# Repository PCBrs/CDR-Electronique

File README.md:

# CDR-Electronique
Carte électronique pour la Coupe de France de robotique de l'équipe PCBrs.

La carte principale est basée sur une Teensy 4.1, la communication est faite par Wi-Fi via un ESP32 et la communication interne du robot via un bus CAN. Les cartes sont modulaires et spécifiques, on peut ajouter plusieurs fois le meme types de cartes il faut juste changer l'ID CAN de la carte en soft. Le microcontroleur des cartes périphériques est un STM32F302C8T6. 

Les cartes ont été conçus sur Kicad.

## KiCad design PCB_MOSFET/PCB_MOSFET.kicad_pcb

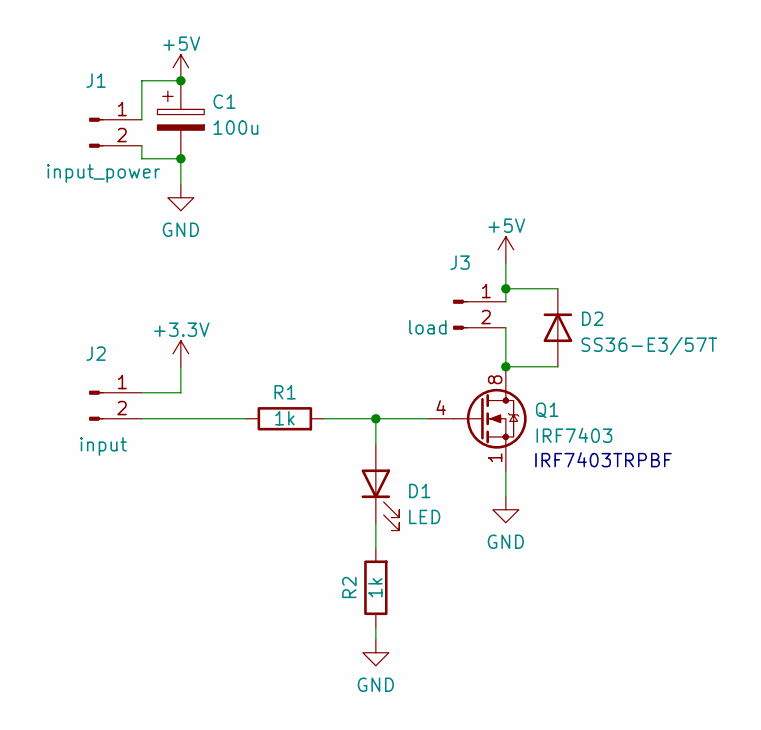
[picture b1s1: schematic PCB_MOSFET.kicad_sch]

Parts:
C1: 100u; CP_Elec_6.3x7.7
D1: LED; LED_0805_2012Metric
D2: SS36-E3/57T; D_SMC
J1: input_power; Wuerth_3.96mm_2pin_645002114822
J2: input; Wuerth_2.54mm_2pins_61900211121
J3: load; Wuerth_3.96mm_2pin_645002114822
Q1: IRF7403; SOIC-8_3.9x4.9mm_P1.27mm
R1, R2: 1k; R_0805_2012Metric

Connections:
+3V3: J2.1
+5V: C1.1, D2.1 (K), J1.1, J3.1
GND: C1.2, J1.2, Q1.1 (S), Q1.2 (S), Q1.3 (S), R2.1
unnamed: D1.1 (K), R2.2
unnamed: D1.2 (A), Q1.4 (G), R1.2
unnamed: D2.2 (A), J3.2, Q1.5 (D), Q1.6 (D), Q1.7 (D), Q1.8 (D)
unnamed: J2.2, R1.1

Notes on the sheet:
IRF7403TRPBF

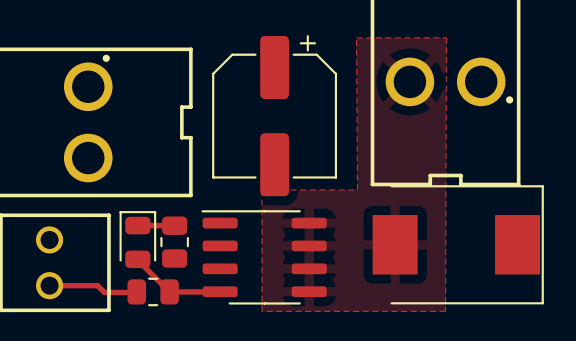
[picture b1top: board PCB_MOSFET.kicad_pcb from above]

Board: 2 copper layers, 9 parts (0 on the bottom side), 6 nets.

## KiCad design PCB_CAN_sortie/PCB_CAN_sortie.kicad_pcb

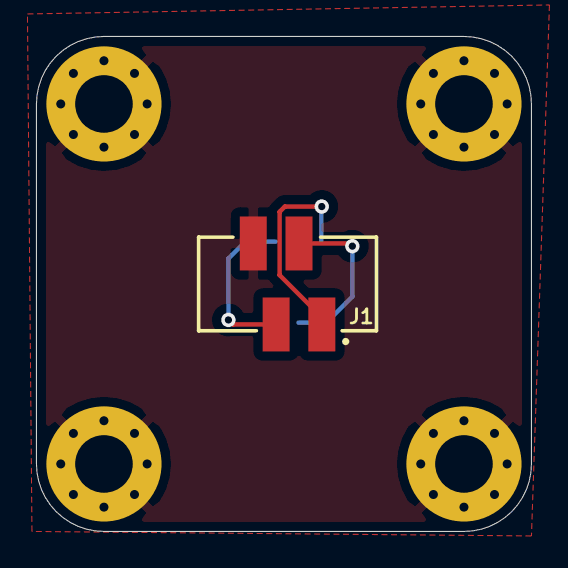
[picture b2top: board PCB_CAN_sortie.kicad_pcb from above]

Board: 2 copper layers, 27.5 x 27.5 mm, 6 parts (1 on the bottom side), 4 nets.

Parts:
H1, H2, H3, H4: .; MountingHole_3.2mm_M3_Pad_Via
J1, J2: CAN; 690367290476

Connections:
+5V: J1.1, J2.1
/CANH: J1.2, J2.2
/CANL: J1.3, J2.3
GND: H1.1, H2.1, H3.1, H4.1, J1.4, J2.4

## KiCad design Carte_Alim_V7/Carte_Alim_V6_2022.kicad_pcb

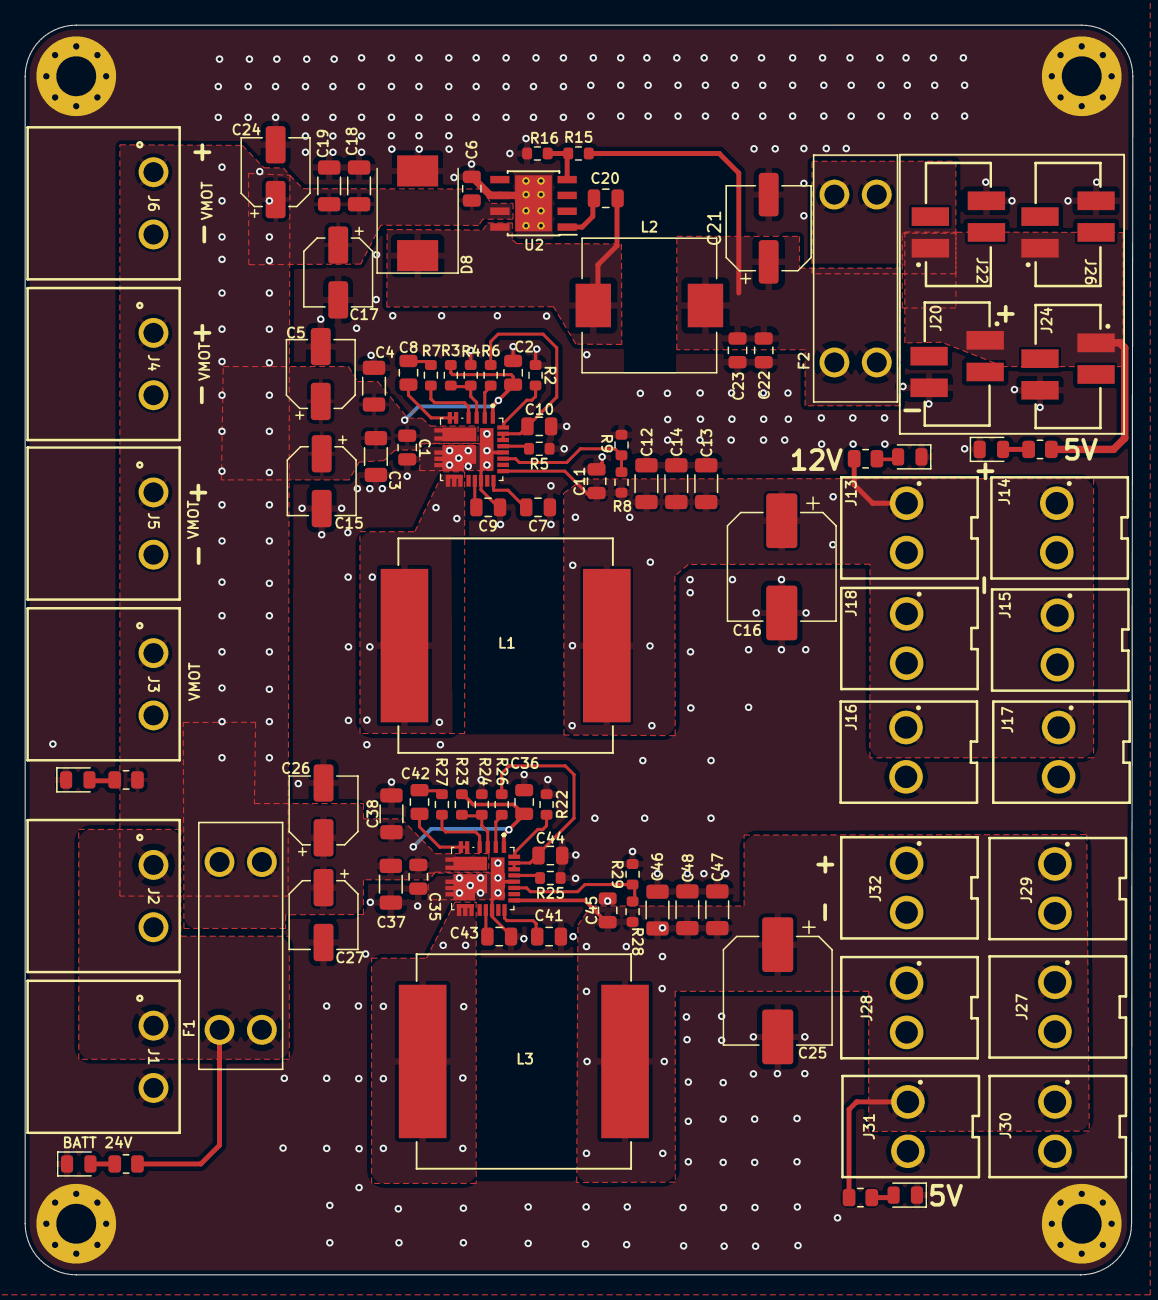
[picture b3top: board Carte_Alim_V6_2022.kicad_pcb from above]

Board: 4 copper layers, 88.9 x 100.3 mm, 102 parts (0 on the bottom side), 39 nets.

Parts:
C1, C2, C6, C8, C11, C22, C35, C36, C42, C45: 100n; C_0805_2012Metric
C3, C4, C12, C13, C14, C18, C19, C37, C38, C46, C47, C48: 22u; C_1206_3216Metric
C5, C15, C17, C24, C26, C27: 10u/50V; CP_Elec_5x5.4
C7, C41: 33n; C_0805_2012Metric
C9, C10, C43, C44: 1u; C_0805_2012Metric
C16, C25: 330u/25V; CP_Elec_8x10.5
C20, C23: 10n; C_0805_2012Metric
C21: 330u; CP_Elec_6.3x7.7
D1, D2, D3, D5, D6: LED; LED_0805_2012Metric
D8: SSC54-E3/9AT; D_SMC
F1, F2: 3557-2; FUSE_3557-2
H1, H2, H3, H4: M3; MountingHole_3.2mm_M3_Pad_Via
J1, J2: BAT_IN; Wuerth_batcon_691313710002
J3, J4, J5, J6: MOT_OUT; Wuerth_batcon_691313710002
J13, J14, J15, J16, J17, J18: 12VP; Wuerth_3.96mm_2pin_645002114822
J20, J22, J24, J26: 5V_CAN; 690367290476
J27, J28, J29, J30, J31, J32: 5VP; Wuerth_3.96mm_2pin_645002114822
L1, L3: 4.7uH; L_Vishay_IHLP-6767
L2: 10uH; L_Wuerth_HCI-1030
R1, R11: 10K; R_0805_2012Metric
R2, R22: 2k; R_0603_1608Metric
R3, R23: 562k; R_0603_1608Metric
R4, R24: 226k; R_0603_1608Metric
R5, R25: 88.7k; R_0603_1608Metric
R6, R26: 100k; R_0603_1608Metric
R7, R27: 3.3; R_0603_1608Metric
R8, R28: 52.3k; R_0603_1608Metric
R9, R15, R29: 10k; R_0603_1608Metric
R10, R30: 10k; R_0805_2012Metric
R13: 560; R_0805_2012Metric
R16: 3k16; R_0603_1608Metric
U1, U3: SIC466ED-T1-GE3; SIC463EDT1GE3
U2: TPS5450ddar; TI_SO-PowerPAD-8_ThermalVias

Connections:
+5P: C25.1, C45.1, C46.1, C47.1, C48.1, J27.1, J28.1, J29.1, J30.1, J31.1, J32.1, L3.2, R28.2, R30.1, U3.20 (VSNS)
+5V: F2.3, J20.1, J22.1, J24.1, J26.1, R13.1
+12P: C11.1, C12.1, C13.1, C14.1, C16.1, J13.1, J14.1, J15.1, J16.1, J17.1, J18.1, L1.2, R8.2, R10.1, U1.20 (VSNS)
+24V: C1.1, C2.1, C3.1, C4.1, C5.1, C6.1, C15.1, C17.1, C18.1, C19.1, C24.1, C26.1, C27.1, C35.1, C36.1, C37.1, C38.1, F1.3, J3.1, J4.1, J5.1, J6.1, R3.1, R11.1, R23.1, U1.1 (VCIN), U1.7 (VIN), U1.8 (VIN), U1.29 (VIN), U2.7 (VIN), U3.1 (VCIN), U3.7 (VIN), U3.8 (VIN), U3.29 (VIN)
+BATT: F1.1, J1.1, J2.1, R1.1
/REGULO2/VDD: C44.2, R26.1, U3.25 (ILIMIT), U3.26 (VDD)
/REGULO5v/VSENS: R15.2, R16.1, U2.4 (VSENSE)
/REGULO/VDD: C10.2, R6.1, U1.25 (ILIMIT), U1.26 (VDD)
GND: C1.2, C2.2, C3.2, C4.2, C5.2, C6.2, C7.2, C9.1, C10.1, C11.2, C12.2, C13.2, C14.2, C15.2, C16.2, C17.2, C18.2, C19.2, C21.2, C22.2, C23.2, C24.2, C25.2, C26.2, C27.2, C35.2, C36.2, C37.2, C38.2, C41.2, C43.1, C44.1, C45.2, C46.2, C47.2, C48.2, D1.1 (K), D2.1 (K), D3.1 (K), D5.1 (K), D6.1 (K), D8.2 (A), H1.1, H2.1, H3.1, H4.1, J1.2, J2.2, J3.2, J4.2, J5.2, J6.2, J13.2, J14.2, J15.2, J16.2, J17.2, J18.2, J20.4, J22.4, J24.4, J26.4, J27.2, J28.2, J29.2, J30.2, J31.2, J32.2, R2.2, R4.2, R5.2, R9.1, R16.2, R22.2, R24.2, R25.2, R29.1, U1.9 (PGND), U1.10 (PGND), U1.11 (PGND), U1.17 (PGND), U1.23 (AGND), U1.28 (AGND), U1.30 (PGND), U1.A30 (PGND), U2.6 (GND), U2.9 (GNDPAD), U3.9 (PGND), U3.10 (PGND), U3.11 (PGND), U3.17 (PGND), U3.23 (AGND), U3.28 (AGND), U3.30 (PGND), U3.A30 (PGND)
unnamed: C7.1, U1.19 (SS)
unnamed: C8.1, R7.2
unnamed: C8.2, U1.5 (PHASE), U1.6 (PHASE)
unnamed: C9.2, U1.16 (VDRV)
unnamed: C20.1, D8.1 (K), L2.1, U2.8 (PH)
unnamed: C20.2, U2.1 (BOOT)
unnamed: C21.1, C22.1, C23.1, F2.1, L2.2, R15.1
unnamed: C41.1, U3.19 (SS)
unnamed: C42.1, R27.2
unnamed: C42.2, U3.5 (PHASE), U3.6 (PHASE)
unnamed: C43.2, U3.16 (VDRV)
unnamed: D1.2 (A), R1.2
unnamed: D2.2 (A), R10.2
unnamed: D3.2 (A), R11.2
unnamed: D5.2 (A), R13.2
unnamed: D6.2 (A), R30.2
unnamed: L1.1, U1.12 (SW), U1.13 (SW), U1.14 (SW), U1.A12
unnamed: L3.1, U3.12 (SW), U3.13 (SW), U3.14 (SW), U3.A12
unnamed: R2.1, U1.27 (MODE)
unnamed: R3.2, R4.1, U1.3 (EN)
unnamed: R5.1, U1.24 (FSW)
unnamed: R6.2, U1.2 (PGOOD)
unnamed: R7.1, U1.4 (BOOT)
unnamed: R8.1, R9.2, U1.22 (VFB)
unnamed: R22.1, U3.27 (MODE)
unnamed: R23.2, R24.1, U3.3 (EN)
unnamed: R25.1, U3.24 (FSW)
unnamed: R26.2, U3.2 (PGOOD)
unnamed: R27.1, U3.4 (BOOT)
unnamed: R28.1, R29.2, U3.22 (VFB)

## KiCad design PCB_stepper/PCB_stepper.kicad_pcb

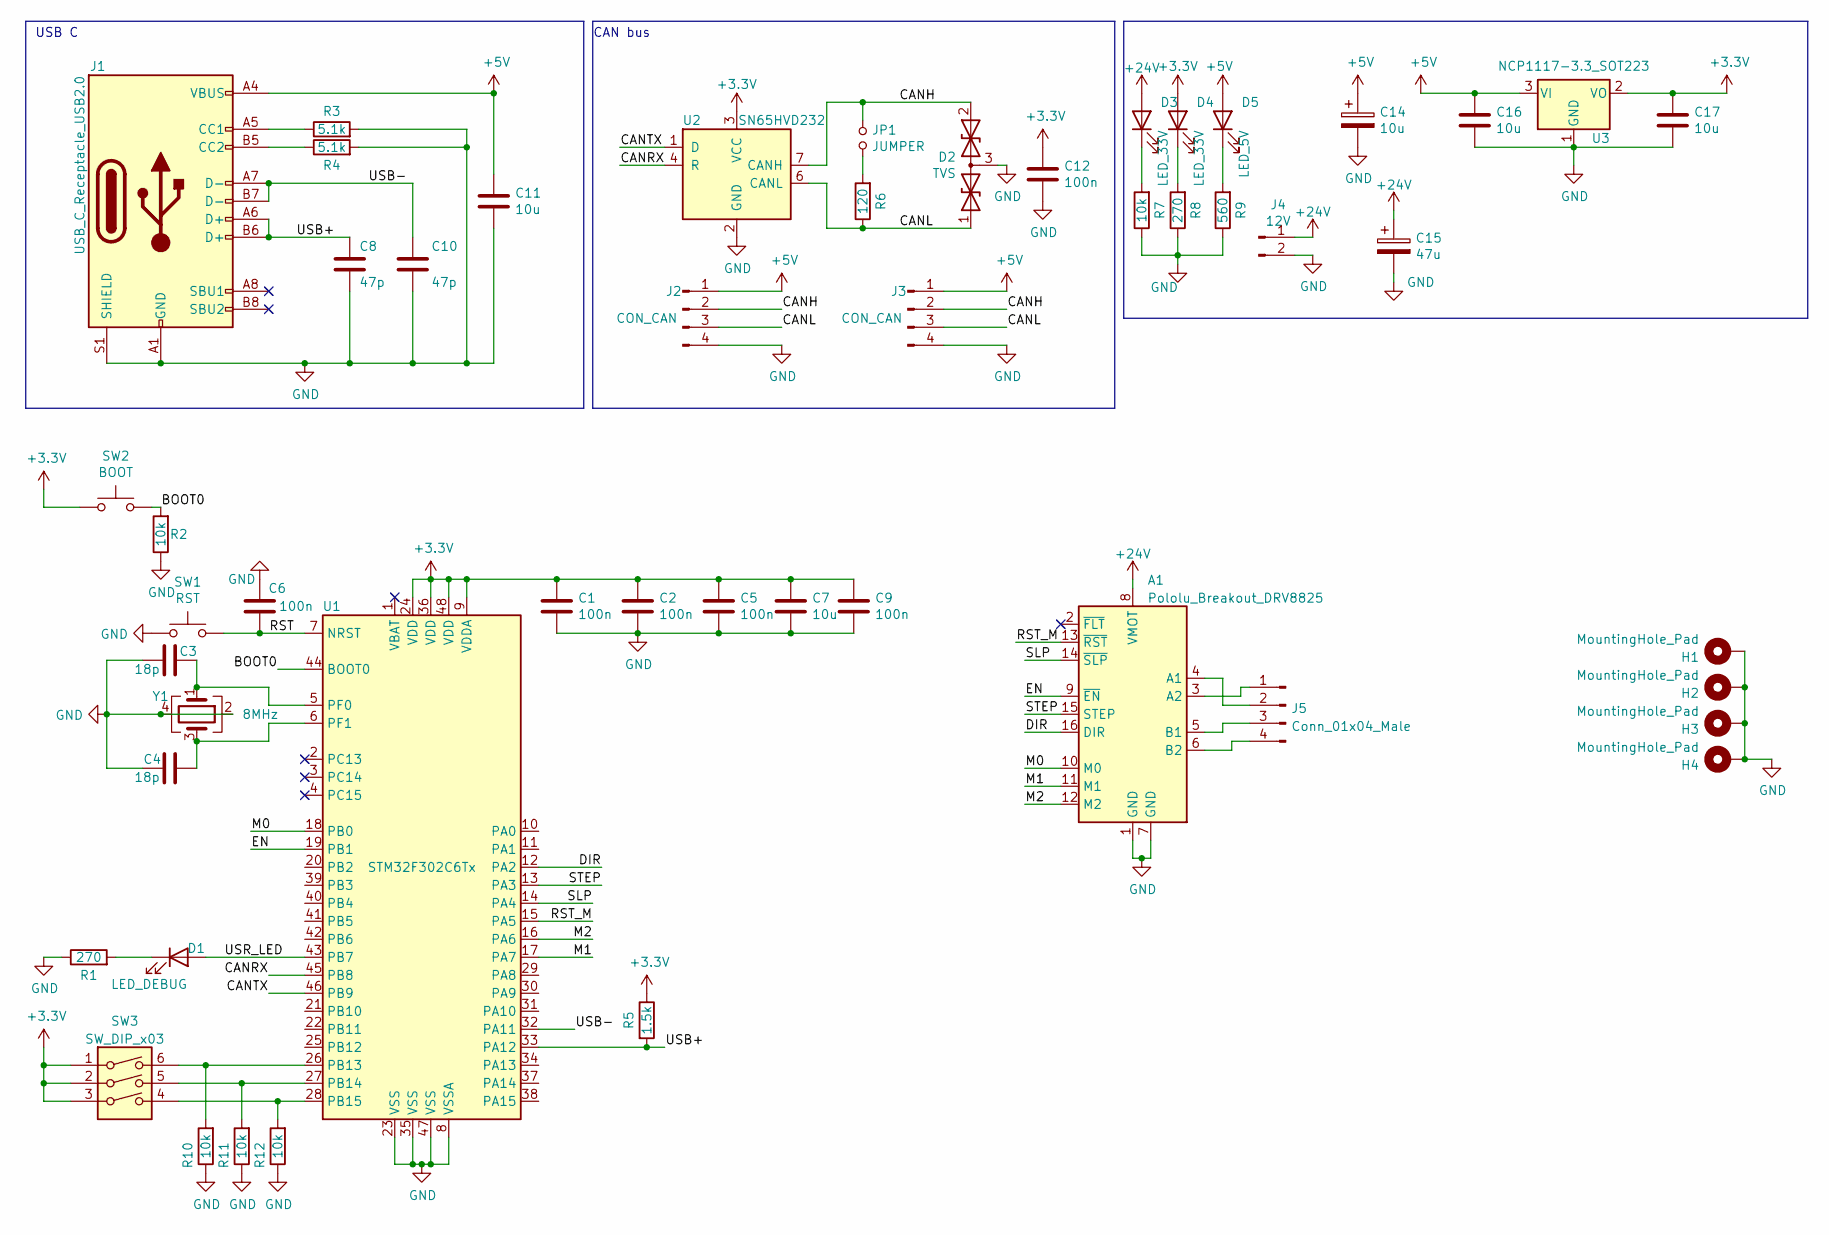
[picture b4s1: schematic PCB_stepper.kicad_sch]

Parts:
A1: Pololu_Breakout_DRV8825; Pololu_Breakout-16_15.2x20.3mm
C1, C2, C5, C6, C9, C12: 100n; C_0805_2012Metric
C3, C4: 18p; C_0805_2012Metric
C7, C11, C16, C17: 10u; C_0805_2012Metric
C8, C10: 47p; C_0805_2012Metric
C14: 10u; CP_Elec_5x5.4
C15: 47u; CP_Elec_6.3x5.4
D1: LED_DEBUG; LED_0805_2012Metric
D2: TVS; SOT-23
D3, D4: LED_33V; LED_0805_2012Metric
D5: LED_5V; LED_0805_2012Metric
H1, H2, H3, H4: MountingHole_Pad; MountingHole_3.2mm_M3_Pad_Via
J1: USB_C_Receptacle_USB2.0; USB_C_Receptacle_GCT_USB4085
J2, J3: CON_CAN; 690367290476
J4: 12V; Wuerth_batcon_691313710002
J5: Conn_01x04_Male; Wuerth_2.54mm_4pins_61900411121
JP1: JUMPER; PinHeader_1x02_P2.54mm_Vertical
R1, R8: 270; R_0805_2012Metric
R2, R7, R10, R11, R12: 10k; R_0805_2012Metric
R3, R4: 5.1k; R_0805_2012Metric
R5: 1.5k; R_0805_2012Metric
R6: 120; R_0805_2012Metric
R9: 560; R_0805_2012Metric
SW1: RST; SW_SPST_CK_RS282G05A3
SW2: BOOT; SW_SPST_CK_RS282G05A3
SW3: SW_DIP_x03; SW_DIP_SPSTx03_Slide_KingTek_DSHP03TJ_W5.25mm_P1.27mm_JPin
U1: STM32F302C6Tx; LQFP-48_7x7mm_P0.5mm
U2: SN65HVD232; SOIC-8_3.9x4.9mm_P1.27mm
U3: NCP1117-3.3_SOT223; SOT-223-3_TabPin2
Y1: 8MHz; Crystal_SMD_5032-4Pin_5.0x3.2mm

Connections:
+3V3: C1.1, C2.1, C5.1, C7.1, C9.1, C12.1, C17.1, D4.2 (A), R5.1, SW2.1, SW3.1, SW3.2, SW3.3, U1.9 (VDDA), U1.24 (VDD), U1.36 (VDD), U1.48 (VDD), U2.3 (VCC), U3.2 (VO)
+5V: C11.1, C14.1, C16.1, D5.2 (A), J1.A4 (VBUS), J1.A9 (VBUS), J1.B4 (VBUS), J1.B9 (VBUS), J2.1, J3.1, U3.3 (VI)
+24V: A1.8 (VMOT), C15.1, D3.2 (A), J4.1
/BOOT0: R2.2, SW2.2, U1.44 (BOOT0)
/CANH: D2.2 (A2), J2.2, J3.2, JP1.1, U2.7 (CANH); also elsewhere on the board
/CANL: D2.1 (A1), J2.3, J3.3, R6.1, U2.6 (CANL)
/CANRX: U1.45 (PB8), U2.4 (R)
/CANTX: U1.46 (PB9), U2.1 (D)
/DIR: A1.16 (DIR), U1.12 (PA2)
/EN: A1.9 (~EN), U1.19 (PB1)
/M0: A1.10 (M0), U1.18 (PB0)
/M1: A1.11 (M1), U1.17 (PA7)
/M2: A1.12 (M2), U1.16 (PA6)
/RST: C6.1, SW1.2, U1.7 (NRST)
/RST_M: A1.13 (~RST), U1.15 (PA5)
/SLP: A1.14 (~SLP), U1.14 (PA4)
/STEP: A1.15 (STEP), U1.13 (PA3)
/USB+: C8.1, J1.A6 (D+), J1.B6 (D+), R5.2, U1.33 (PA12)
/USB-: C10.1, J1.A7 (D-), J1.B7 (D-), U1.32 (PA11)
/USR_LED: D1.2 (A), U1.43 (PB7)
GND: A1.1 (GND), A1.7 (GND), C1.2, C2.2, C3.2, C4.2, C5.2, C6.2, C7.2, C8.2, C9.2, C10.2, C11.2, C12.2, C14.2, C15.2, C16.2, C17.2, D2.3 (common), H1.1, H2.1, H3.1, H4.1, J1.A1 (GND), J1.A12 (GND), J1.B1 (GND), J1.B12 (GND), J1.S1 (SHIELD), J2.4, J3.4, J4.2, R1.1, R2.1, R3.2, R4.2, R7.1, R8.1, R9.1, R10.1, R11.1, R12.1, SW1.1, U1.8 (VSSA), U1.23 (VSS), U1.35 (VSS), U1.47 (VSS), U2.2 (GND), U3.1 (GND), Y1.2, Y1.4
unnamed: A1.3 (A2), J5.1
unnamed: A1.4 (A1), J5.2
unnamed: A1.5 (B1), J5.3
unnamed: A1.6 (B2), J5.4
unnamed: C3.1, U1.5 (PF0), Y1.1
unnamed: C4.1, U1.6 (PF1), Y1.3
unnamed: D1.1 (K), R1.2
unnamed: D3.1 (K), R7.2
unnamed: D4.1 (K), R8.2
unnamed: D5.1 (K), R9.2
unnamed: J1.A5 (CC1), R3.1
unnamed: J1.B5 (CC2), R4.1
unnamed 33: JP1.2, R6.2; also elsewhere on the board
unnamed: R10.2, SW3.6, U1.26 (PB13)
unnamed: R11.2, SW3.5, U1.27 (PB14)
unnamed: R12.2, SW3.4, U1.28 (PB15)

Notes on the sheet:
USB C
CAN bus

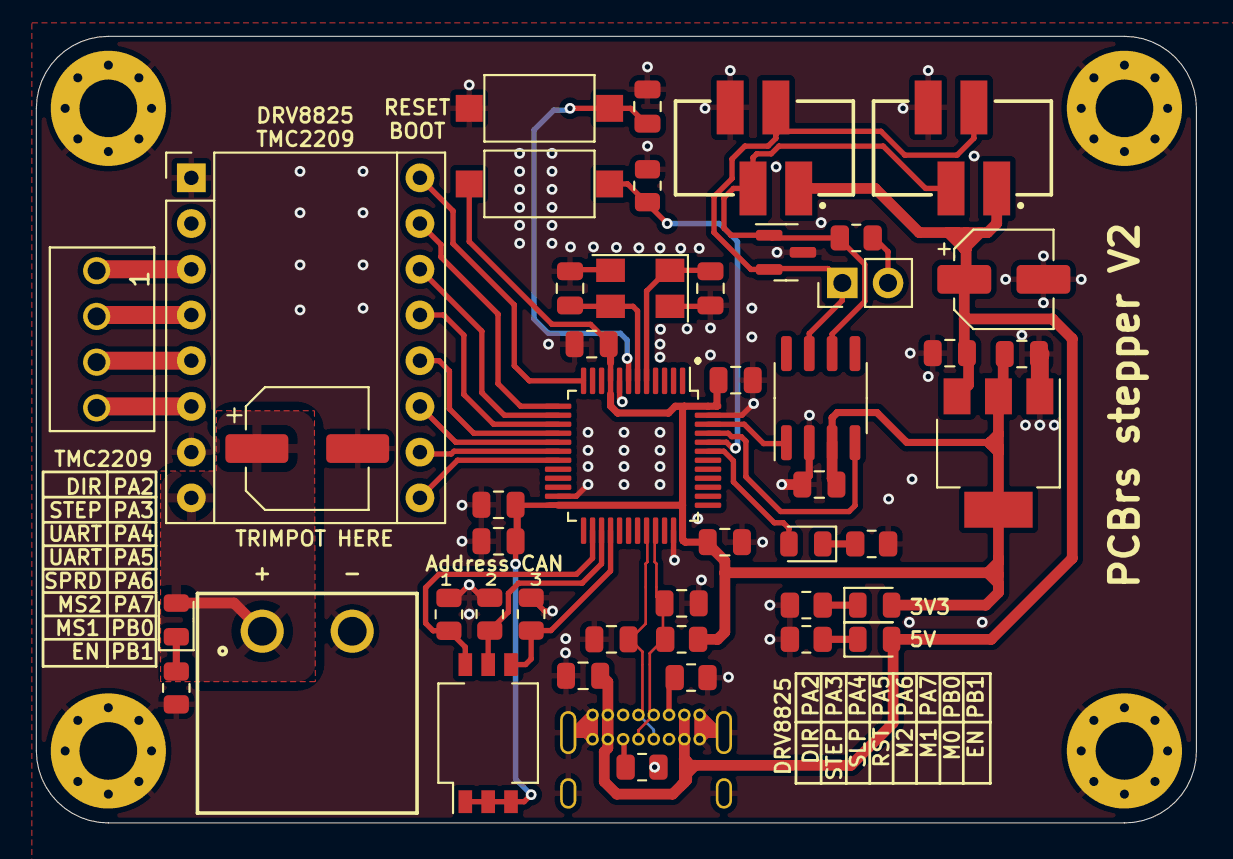
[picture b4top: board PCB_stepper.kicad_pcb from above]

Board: 2 copper layers, 64.4 x 43.7 mm, 51 parts (1 on the bottom side), 37 nets.

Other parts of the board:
120: JUMPER; PinHeader_1x02_P2.54mm_Vertical

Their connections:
/CANH: 120.1; also elsewhere on the board
unnamed 33: 120.2; also elsewhere on the board

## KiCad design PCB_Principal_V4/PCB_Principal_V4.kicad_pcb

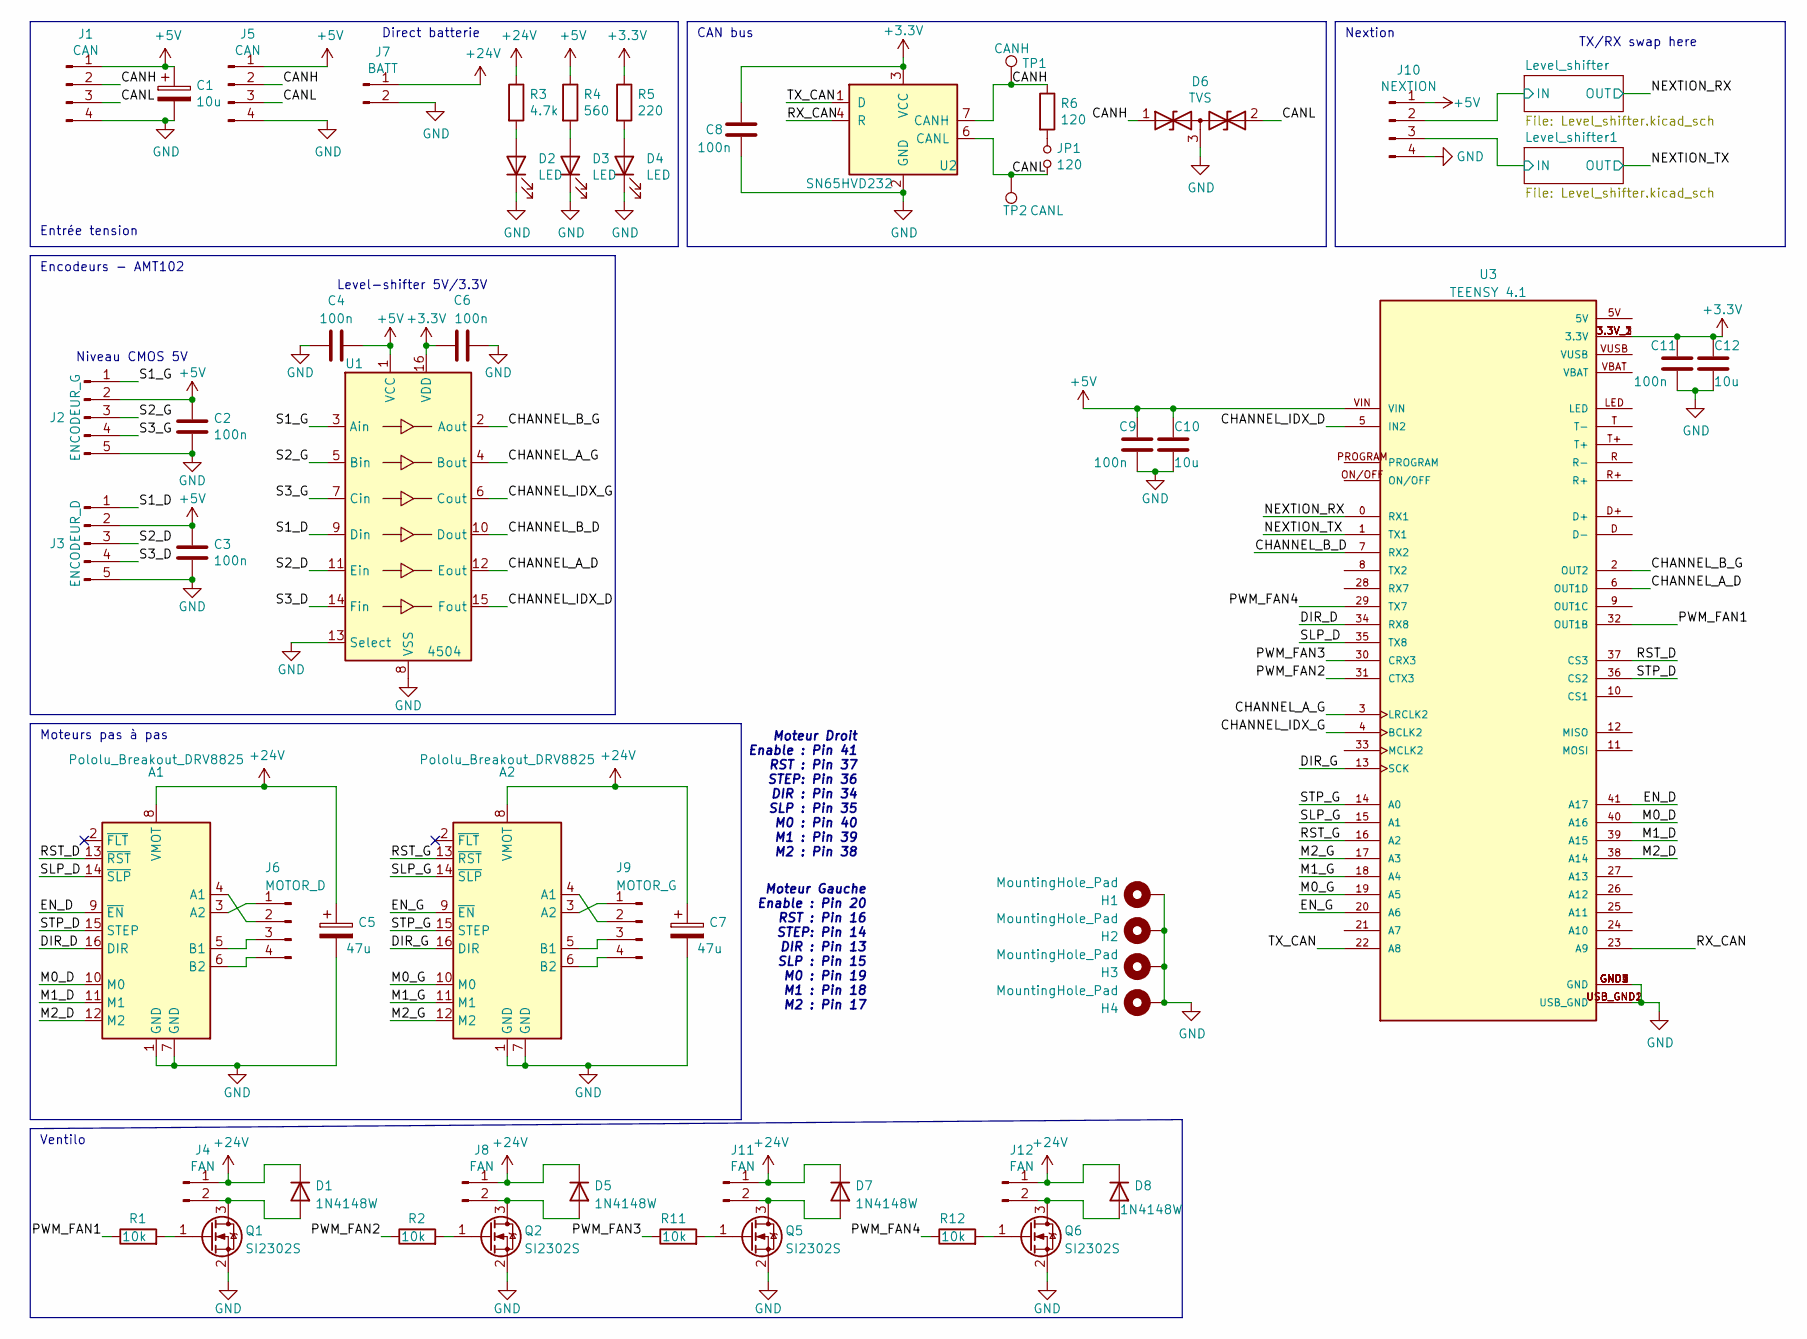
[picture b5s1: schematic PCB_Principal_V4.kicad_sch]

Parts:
A1, A2: Pololu_Breakout_DRV8825; Pololu_Breakout-16_15.2x20.3mm
C1: 10u; CP_Elec_5x5.4
C2, C3, C4, C6, C8, C9, C11: 100n; C_0805_2012Metric_Pad1.18x1.45mm_HandSolder
C5, C7: 47u; CP_Elec_6.3x5.4
C10, C12: 10u; C_0805_2012Metric_Pad1.18x1.45mm_HandSolder
D1, D5, D7, D8: 1N4148W; D_SOD-123
D2, D3, D4: LED; LED_0805_2012Metric_Pad1.15x1.40mm_HandSolder
D6: TVS; SOT-23
H1, H2, H3, H4: MountingHole_Pad; MountingHole_3.2mm_M3_Pad_Via
J1, J5: CAN; 690367290476
J2: ENCODEUR_G; PinHeader_1x05_P2.54mm_Vertical
J3: ENCODEUR_D; PinHeader_1x05_P2.54mm_Vertical
J4, J8, J11, J12: FAN; Wuerth_2.54mm_2pins_61900211121
J6: MOTOR_D; Wuerth_2.54mm_4pins_61900411121
J7: BATT; Wuerth_batcon_691313710002
J9: MOTOR_G; Wuerth_2.54mm_4pins_61900411121
J10: NEXTION; Wuerth_2.54mm_4pins_61900411121
JP1: 120; PinHeader_1x02_P2.54mm_Vertical
Q1, Q2, Q5, Q6: SI2302S; SOT-23
R1, R2, R11, R12: 10k; R_0805_2012Metric_Pad1.20x1.40mm_HandSolder
R3: 4.7k; R_0805_2012Metric_Pad1.20x1.40mm_HandSolder
R4: 560; R_0805_2012Metric_Pad1.20x1.40mm_HandSolder
R5: 220; R_0805_2012Metric_Pad1.20x1.40mm_HandSolder
R6: 120; R_0805_2012Metric_Pad1.20x1.40mm_HandSolder
TP1: CANH; TestPoint_Pad_D1.0mm
TP2: CANL; TestPoint_Pad_D1.0mm
U1: 4504; TSSOP-16_4.4x5mm_P0.65mm
U2: SN65HVD232; SOIC-8_3.9x4.9mm_P1.27mm
U3: TEENSY 4.1; Teensy_4-1; PARTREV 4.1

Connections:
+3V3: C6.2, C8.2, C11.1, C12.1, R5.1, U1.16 (VDD), U2.3 (VCC), U3.3.3V_1 (3.3V), U3.3.3V_2 (3.3V), U3.3.3V_3 (3.3V); also elsewhere on the board
+5V: C1.1, C2.1, C3.1, C4.2, C9.1, C10.1, J1.1, J2.2, J3.2, J5.1, J10.1, R4.1, U1.1 (VCC), U3.VIN; also elsewhere on the board
+24V: A1.8 (VMOT), A2.8 (VMOT), C5.1, C7.1, D1.1 (K), D5.1 (K), D7.1 (K), D8.1 (K), J4.1, J7.1, J8.1, J11.1, J12.1, R3.1
/CANH: D6.1 (A1), J1.2, J5.2, R6.1, TP1.1, U2.7 (CANH)
/CANL: D6.2 (A2), J1.3, J5.3, JP1.2, TP2.1, U2.6 (CANL)
/CHANNEL_A_D: U1.12 (Eout), U3.6 (OUT1D)
/CHANNEL_A_G: U1.4 (Bout), U3.3 (LRCLK2)
/CHANNEL_B_D: U1.10 (Dout), U3.7 (RX2)
/CHANNEL_B_G: U1.2 (Aout), U3.2 (OUT2)
/CHANNEL_IDX_D: U1.15 (Fout), U3.5 (IN2)
/CHANNEL_IDX_G: U1.6 (Cout), U3.4 (BCLK2)
/DIR_D: A1.16 (DIR), U3.34 (RX8)
/DIR_G: A2.16 (DIR), U3.13 (SCK)
/EN_D: A1.9 (~EN), U3.41 (A17)
/EN_G: A2.9 (~EN), U3.20 (A6)
/Level_shifter1/IN: J10.3; also elsewhere on the board
/Level_shifter/IN: J10.2; also elsewhere on the board
/M0_D: A1.10 (M0), U3.40 (A16)
/M0_G: A2.10 (M0), U3.19 (A5)
/M1_D: A1.11 (M1), U3.39 (A15)
/M1_G: A2.11 (M1), U3.18 (A4)
/M2_D: A1.12 (M2), U3.38 (A14)
/M2_G: A2.12 (M2), U3.17 (A3)
/NEXTION_RX: U3.0 (RX1); also elsewhere on the board
/NEXTION_TX: U3.1 (TX1); also elsewhere on the board
/PWM_FAN1: R1.1, U3.32 (OUT1B)
/PWM_FAN2: R2.1, U3.31 (CTX3)
/PWM_FAN3: R11.1, U3.30 (CRX3)
/PWM_FAN4: R12.1, U3.29 (TX7)
/RST_D: A1.13 (~RST), U3.37 (CS3)
/RST_G: A2.13 (~RST), U3.16 (A2)
/RX_CAN: U2.4 (R), U3.23 (A9)
/S1_D: J3.1, U1.9 (Din)
/S1_G: J2.1, U1.3 (Ain)
/S2_D: J3.3, U1.11 (Ein)
/S2_G: J2.3, U1.5 (Bin)
/S3_D: J3.4, U1.14 (Fin)
/S3_G: J2.4, U1.7 (Cin)
/SLP_D: A1.14 (~SLP), U3.35 (TX8)
/SLP_G: A2.14 (~SLP), U3.15 (A1)
/STP_D: A1.15 (STEP), U3.36 (CS2)
/STP_G: A2.15 (STEP), U3.14 (A0)
/TX_CAN: U2.1 (D), U3.22 (A8)
GND: A1.1 (GND), A1.7 (GND), A2.1 (GND), A2.7 (GND), C1.2, C2.2, C3.2, C4.1, C5.2, C6.1, C7.2, C8.1, C9.2, C10.2, C11.2, C12.2, D2.1 (K), D3.1 (K), D4.1 (K), D6.3 (common), H1.1, H2.1, H3.1, H4.1, J1.4, J2.5, J3.5, J5.4, J7.2, J10.4, Q1.2 (E), Q2.2 (E), Q5.2 (E), Q6.2 (E), U1.8 (VSS), U1.13 (Select), U2.2 (GND), U3.GND1 (GND), U3.GND2 (GND), U3.GND3 (GND), U3.GND4 (GND), U3.GND5 (GND), U3.USB_GND1 (USB_GND), U3.USB_GND2 (USB_GND)
unnamed: A1.3 (A2), J6.1
unnamed: A1.4 (A1), J6.2
unnamed: A1.5 (B1), J6.3
unnamed: A1.6 (B2), J6.4
unnamed: A2.3 (A2), J9.1
unnamed: A2.4 (A1), J9.2
unnamed: A2.5 (B1), J9.3
unnamed: A2.6 (B2), J9.4
unnamed: D1.2 (A), J4.2, Q1.3 (C)
unnamed: D2.2 (A), R3.2
unnamed: D3.2 (A), R4.2
unnamed: D4.2 (A), R5.2
unnamed: D5.2 (A), J8.2, Q2.3 (C)
unnamed: D7.2 (A), J11.2, Q5.3 (C)
unnamed: D8.2 (A), J12.2, Q6.3 (C)
unnamed: JP1.1, R6.2
unnamed: Q1.1 (B), R1.2
unnamed: Q2.1 (B), R2.2
unnamed: Q5.1 (B), R11.2
unnamed: Q6.1 (B), R12.2

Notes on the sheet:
Ventilo
Direct batterie
TX/RX swap here
Level-shifter 5V/3.3V
Moteur Gauche Enable : Pin 20 RST : Pin 16 STEP: Pin 14 DIR : Pin 13 SLP : Pin 15 M0 : Pin 19 M1 : Pin 18 M2 : Pin 17
Entrée tension
Nextion
CAN bus
Encodeurs - AMT102
Niveau CMOS 5V
Moteurs pas à pas
Moteur Droit Enable : Pin 41 RST : Pin 37 STEP: Pin 36 DIR : Pin 34 SLP : Pin 35 M0 : Pin 40 M1 : Pin 39 M2 : Pin 38

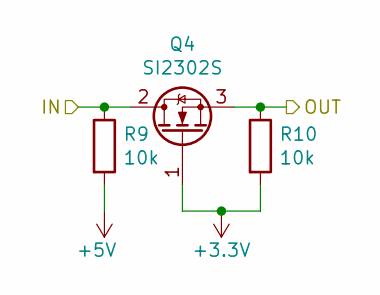
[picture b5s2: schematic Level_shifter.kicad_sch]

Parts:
Q4: SI2302S; SOT-23
R9, R10: 10k; R_0805_2012Metric_Pad1.20x1.40mm_HandSolder

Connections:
+3V3: Q4.1 (G), R10.2; also elsewhere on the board
+5V: R9.2; also elsewhere on the board
/Level_shifter/IN: Q4.2 (D), R9.1; also elsewhere on the board
/NEXTION_RX: Q4.3 (S), R10.1; also elsewhere on the board

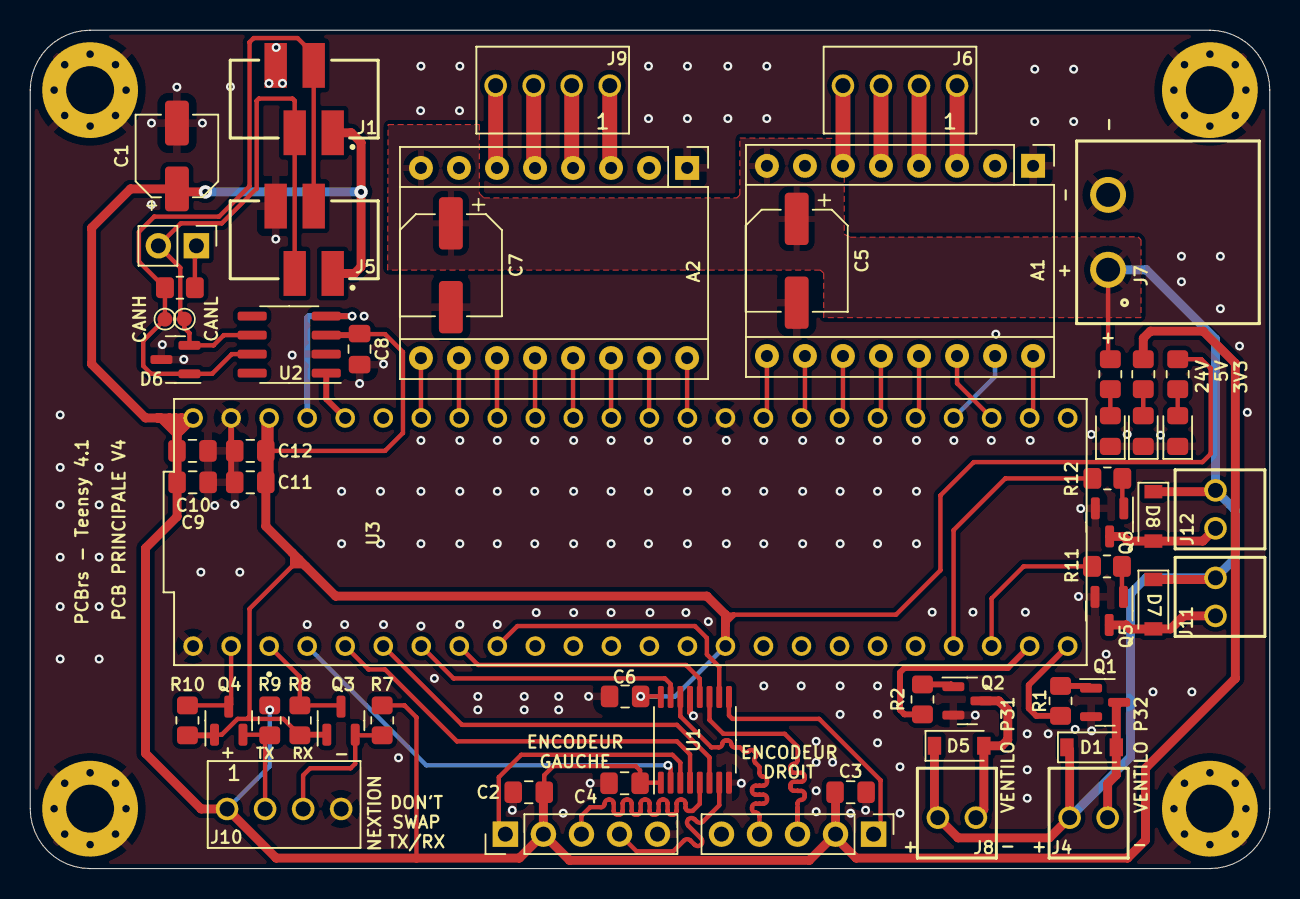
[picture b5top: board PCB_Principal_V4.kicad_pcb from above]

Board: 2 copper layers, 82.8 x 56.0 mm, 62 parts (0 on the bottom side), 64 nets.

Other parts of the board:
Q3: SI2302S; SOT-23
R7, R8: 10k; R_0805_2012Metric_Pad1.20x1.40mm_HandSolder

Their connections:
+3V3: Q3.1 (G), R8.2; also elsewhere on the board
+5V: R7.2; also elsewhere on the board
/Level_shifter1/IN: Q3.2 (D), R7.1; also elsewhere on the board
/NEXTION_TX: Q3.3 (S), R8.1; also elsewhere on the board

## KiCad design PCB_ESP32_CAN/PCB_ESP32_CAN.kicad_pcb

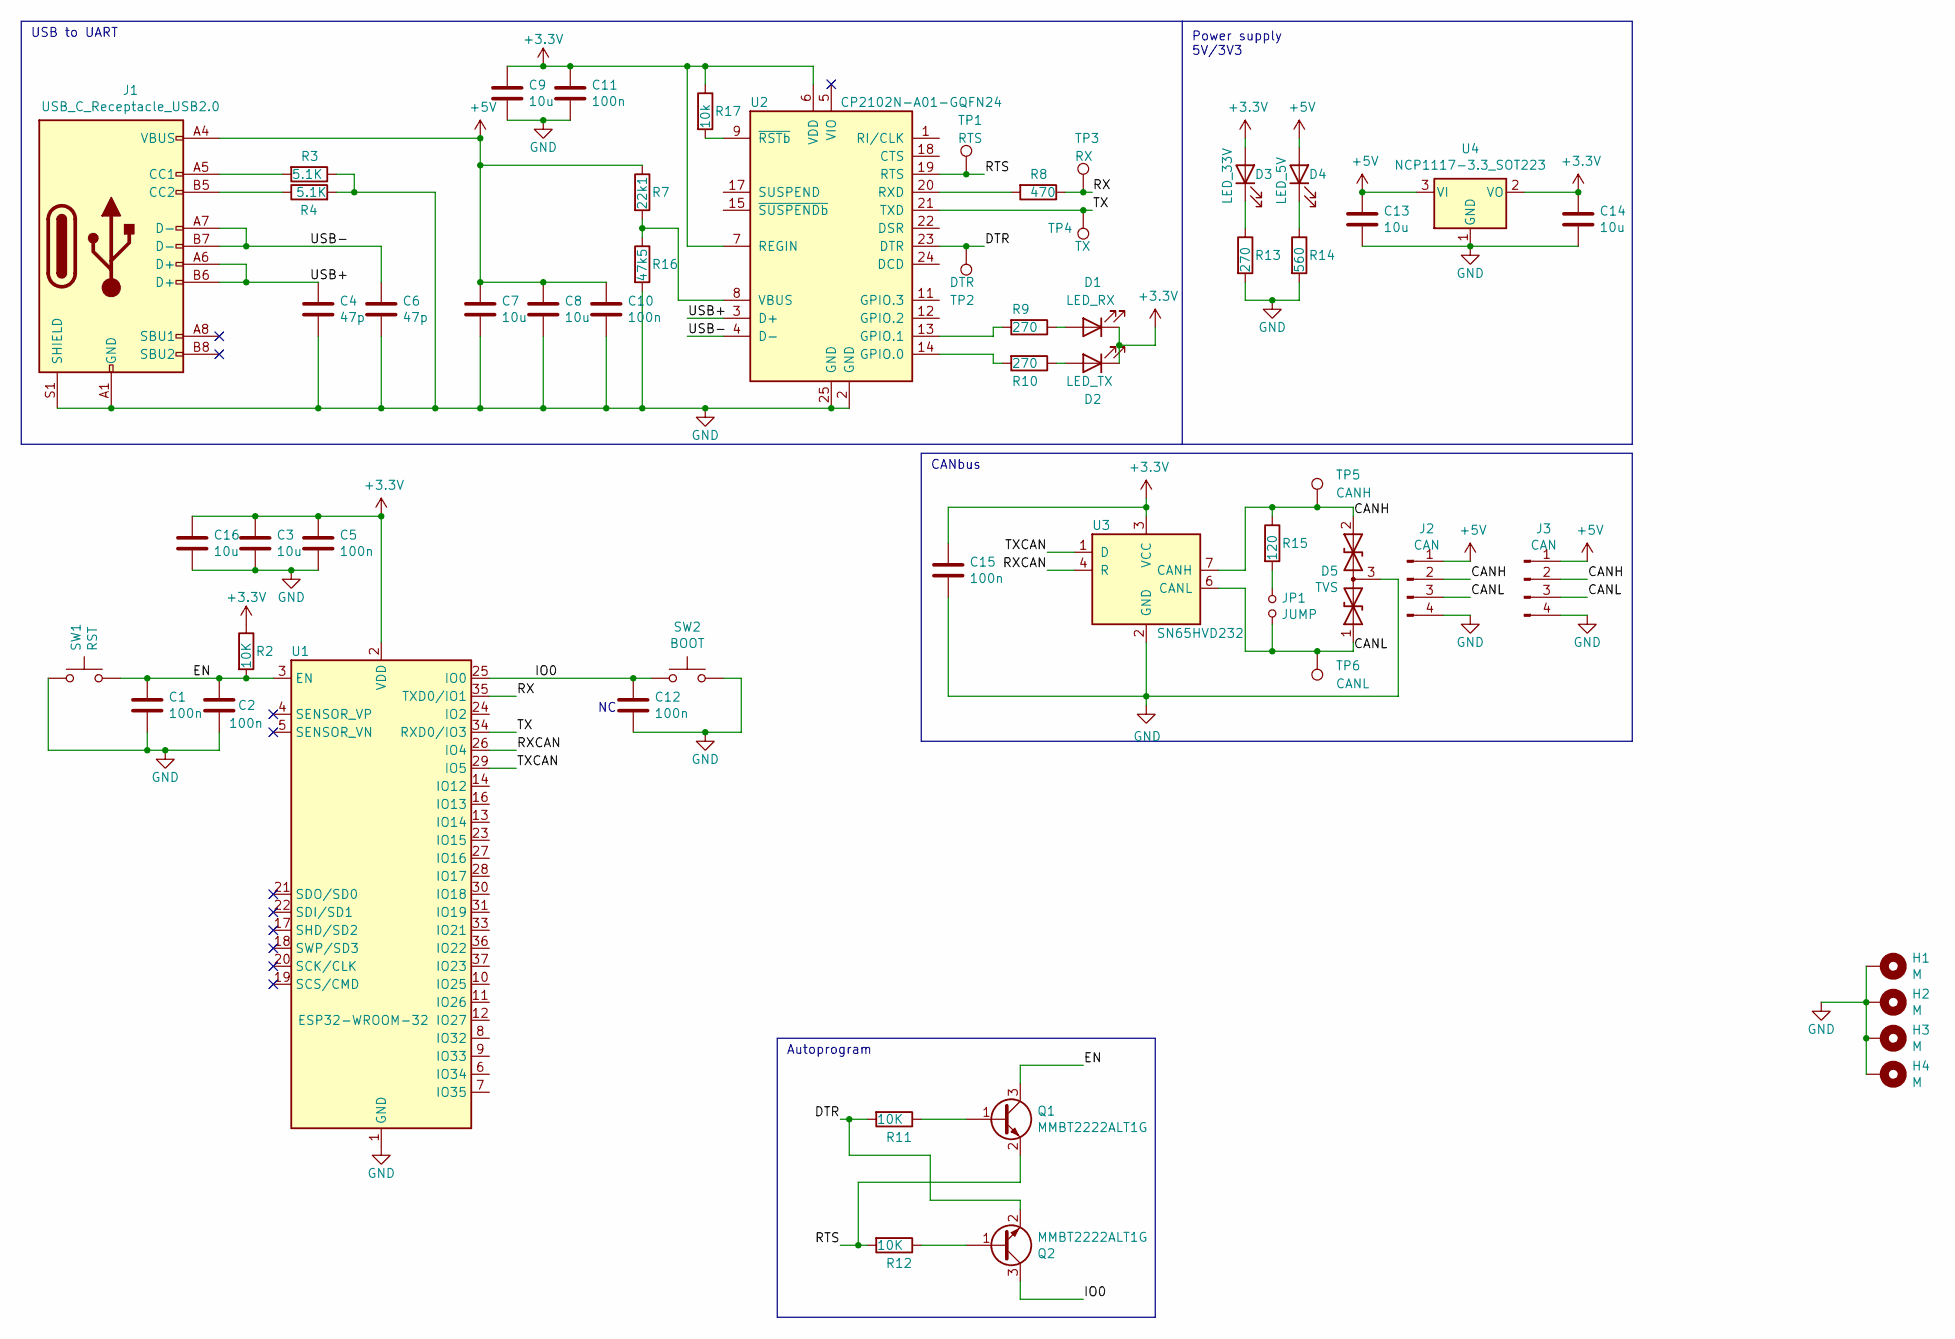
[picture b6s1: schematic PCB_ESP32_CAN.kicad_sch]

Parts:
C1, C2, C5, C10, C11, C12, C15: 100n; C_0805_2012Metric
C3, C7, C8, C9, C13, C14, C16: 10u; C_0805_2012Metric
C4, C6: 47p; C_0805_2012Metric
D1: LED_RX; LED_0805_2012Metric
D2: LED_TX; LED_0805_2012Metric
D3: LED_33V; LED_0805_2012Metric
D4: LED_5V; LED_0805_2012Metric
D5: TVS; SOT-23
H1, H2, H3, H4: M; MountingHole_3.2mm_M3_Pad_Via
J1: USB_C_Receptacle_USB2.0; USB_C_Receptacle_GCT_USB4085
J2, J3: CAN; 690367290476
JP1: JUMP; PinHeader_1x02_P2.54mm_Vertical
Q1, Q2: MMBT2222ALT1G; SOT-23
R2, R11, R12: 10K; R_0805_2012Metric
R3, R4: 5.1K; R_0805_2012Metric
R7: 22k1; R_0805_2012Metric
R8: 470; R_0805_2012Metric
R9, R10, R13: 270; R_0805_2012Metric
R14: 560; R_0805_2012Metric
R15: 120; R_0805_2012Metric
R16: 47k5; R_0805_2012Metric
R17: 10k; R_0805_2012Metric
SW1: RST; SW_SPST_FSMSM
SW2: BOOT; SW_SPST_FSMSM
TP1: RTS; TestPoint_Pad_D1.0mm
TP2: DTR; TestPoint_Pad_D1.0mm
TP3: RX; TestPoint_Pad_D1.0mm
TP4: TX; TestPoint_Pad_D1.0mm
TP5: CANH; TestPoint_Pad_D1.0mm
TP6: CANL; TestPoint_Pad_D1.0mm
U1: ESP32-WROOM-32
U2: CP2102N-A01-GQFN24; QFN-24-1EP_4x4mm_P0.5mm_EP2.6x2.6mm
U3: SN65HVD232; SOIC-8_3.9x4.9mm_P1.27mm
U4: NCP1117-3.3_SOT223; SOT-223-3_TabPin2

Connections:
+3V3: C3.1, C5.1, C9.1, C11.1, C14.1, C15.1, C16.1, D1.1 (K), D2.1 (K), D3.2 (A), R2.1, R17.1, U1.2 (VDD), U2.6 (VDD), U2.7 (REGIN), U3.3 (VCC), U4.2 (VO)
+5V: C7.1, C8.1, C10.1, C13.1, D4.2 (A), J1.A4 (VBUS), J1.A9 (VBUS), J1.B4 (VBUS), J1.B9 (VBUS), J2.1, J3.1, R7.1, U4.3 (VI)
/CANH: D5.2 (A2), J2.2, J3.2, R15.1, TP5.1, U3.7 (CANH)
/CANL: D5.1 (A1), J2.3, J3.3, JP1.2, TP6.1, U3.6 (CANL)
/DTR: Q2.2 (E), R11.2, TP2.1, U2.23 (DTR)
/EN: C1.1, C2.2, Q1.3 (C), R2.2, SW1.2, U1.3 (EN)
/IO0: C12.1, Q2.3 (C), SW2.1, U1.25 (IO0)
/RTS: Q1.2 (E), R12.2, TP1.1, U2.19 (RTS)
/RX: R8.1, TP3.1, U1.35 (TXD0/IO1)
/RXCAN: U1.26 (IO4), U3.4 (R)
/TX: TP4.1, U1.34 (RXD0/IO3), U2.21 (TXD)
/TXCAN: U1.29 (IO5), U3.1 (D)
/USB+: C4.1, J1.A6 (D+), J1.B6 (D+), U2.3 (D+)
/USB-: C6.1, J1.A7 (D-), J1.B7 (D-), U2.4 (D-)
GND: C1.2, C2.1, C3.2, C4.2, C5.2, C6.2, C7.2, C8.2, C9.2, C10.2, C11.2, C12.2, C13.2, C14.2, C15.2, C16.2, D5.3 (common), H1.1, H2.1, H3.1, H4.1, J1.A1 (GND), J1.A12 (GND), J1.B1 (GND), J1.B12 (GND), J1.S1 (SHIELD), J2.4, J3.4, R3.1, R4.2, R13.2, R14.2, R16.2, SW1.1, SW2.2, U1.1 (GND), U1.15 (GND), U1.38 (GND), U1.39 (GND), U2.2 (GND), U2.25 (GND), U3.2 (GND), U4.1 (GND)
unnamed: D1.2 (A), R9.1
unnamed: D2.2 (A), R10.1
unnamed: D3.1 (K), R13.1
unnamed: D4.1 (K), R14.1
unnamed: J1.A5 (CC1), R3.2
unnamed: J1.B5 (CC2), R4.1
unnamed: JP1.1, R15.2
unnamed: Q1.1 (B), R11.1
unnamed: Q2.1 (B), R12.1
unnamed: R8.2, U2.20 (RXD)
unnamed: R9.2, U2.13 (GPIO.1)
unnamed: R10.2, U2.14 (GPIO.0)
unnamed: R7.2, R16.1, U2.8 (VBUS)
unnamed: R17.2, U2.9 (~RSTb)

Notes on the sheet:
CANbus
Autoprogram
USB to UART
Power supply 5V/3V3
